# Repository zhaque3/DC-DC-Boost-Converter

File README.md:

# DC Boost Board

**Project:** DC Boost Board — a programmable boost converter for the University of Alberta EcoCar 2025 Prototype Vehicle. The vehicle (Sally) won first place at the Shell Eco Marathon 2025 in the Hydrogen Fuel Cell Prototype Category. 

**Purpose:** This board takes the vehicle's hydrogen fuel cell output voltage (nominally 24 V) and provides a controllable boosted output (typical target: 48 V) for the motor controller and motor. It includes measurement (voltage/current sensing), safety/protection (eFuses and monitoring), an MCU running FreeRTOS for control and telemetry, a simple local UI (OLED + push buttons), and CAN bus communication with other boards on the vehicle and wireless base station.

---

## Table of contents

1. [Key features](#key-features)
2. [Hardware details](#hardware-details)
3. [FreeRTOS firmware overview](#freertos-firmware-overview-what-is-actually-running-on-board)

---

## Key features

* **LM5123** synchronous boost controller driving external mosfets for high-efficiency boost operation.
* Programmable dynamic voltage tuning controlled by MCU and local UI.
* Input/Output: nominal 24 V. The board is designed to output 48V but is capable of outputting 57. 
* **Input / output voltage sensing** and **current sensing** using ADCs and filtering. Firmware computes averaged values before publishing them to the display and logs.
* **TPS2623 eFuses** for controlled power delivery and overcurrent protection.
* **Local UI**: small OLED display (SSD1306) + push buttons for interaction. The display shows input/output voltages, currents, and an effeciency score.
* **FreeRTOS-based firmware** with multiple tasks handling ADC acquisition, DAC control for the tracking/virtual voltage (TRK) pin, LED/status handling, screen updates, and CAN bus communication.

---

## Hardware details

### Synchronous boost controller

* The Texas Instruments LM5123 is used as the switching controller. It drives external mosfets located at the back of the board. The 4 high and low side mosfets can be place on this board. 
* The ENABLE pin from the boost controller is driven by the MCU to allow safe startup/shutdown sequences (the code waits until input voltage is above a small threshold, then toggles ENABLE with a startup delay).
* The TRK (tracking) reference to the controller is driven by the MCU DAC to set the desired output. The firmware converts the `SET_VOLT` value to an appropriate DAC code.

### Sensing

* Voltage sensing is implemented with resistor dividers feeding ADCs.
* Current sensing is performed by hall-effect current sensors that outputs an ADC value to the MCU. 
* ADC sampling is done via DMA for efficiency

### Microcontroller

* The board is built around an STM32G91KUE6 microcontroller, which serves as the central control, sensing, and communication unit for the boost system.
* The MCU runs a FreeRTOS-based firmware architecture, allowing concurrent handling of power control, sensing, UI updates, and CAN communication without blocking critical control paths.

---

## FreeRTOS firmware overview

The firmware running on the DC Boost Board is FreeRTOS based and implemented entirely in `app_freertos.c`.  
The system is structured as a set of independent FreeRTOS tasks, each responsible for a specific functional domain: power control, sensing, user interface, and vehicle communication.

## Tasks (as implemented in `app_freertos.c`)

### DefaultTask (`StartDefaultTask`)

- Initializes the USB CDC device at startup for debug telemetry.
- Implements ENABLE pin sequencing for the LM5123 boost controller:
  - Continuously monitors input voltage.
  - Applies a one-time startup delay before asserting ENABLE once sufficient input voltage is detected.
  - Forces ENABLE low if input voltage falls below threshold and resets the startup sequence.
- Handles a push-button input to increment the output voltage setpoint (`SET_VOLT`) with bounds checking based on input voltage.

### ADC Conversion Task (`StartAdcConv`)

- Starts **ADC peripherals with DMA** for continuous sampling.
- Measures:
  - Input voltage
  - Output voltage
  - Input current
  - Output current
- Applies a 50-sample moving average to current measurements for noise reduction.
- Computes a real-time efficiency estimate using measured voltage and current values.
- Publishes computed values into CAN data structures and prints debug telemetry over USB CDC.

### Screen Print Task (`startScreenPrint`)

- Drives an **SSD1306 OLED display**.
- Displays:
  - Voltage setpoint
  - Input and output voltages
  - Input and output currents
  - Computed efficiency
- When a fault or lock condition is received over CAN, the display switches to an alarm state.

### TRK Pin Control Task (`StartTRKPin`)

- Controls the LM5123 TRK (tracking) pin using the on-chip DAC.
- Converts `SET_VOLT` into a proportional DAC output corresponding to the desired boost output voltage.

### Status LED Task (`StartStatusLED`)

- Controls multiple PWM-driven status LEDs using STM32 timer peripherals.
- LED indications include:
  - Boost ENABLE state
  - General system activity
- Continuously monitors the ENABLE GPIO to synchronize LED states with actual hardware behavior.

## CAN Bus Communication

- Uses the STM32 FDCAN peripheral for vehicle network communication.
- CAN reception is interrupt-driven and handled via the RX FIFO callback, with received frames pushed into FreeRTOS message queues.
- A dedicated receive task parses incoming CAN messages to:
  - Detect fault or lock conditions (e.g. hydrogen alarm states).
  - Update system behavior and UI state.
- A dedicated transmit task periodically publishes:
  - Input and output voltages
  - Input and output currents
  - Efficiency
  - System status flags
- CAN messaging enables real-time monitoring by other PCB's on the vehicle and the wireless telemetry system.

---

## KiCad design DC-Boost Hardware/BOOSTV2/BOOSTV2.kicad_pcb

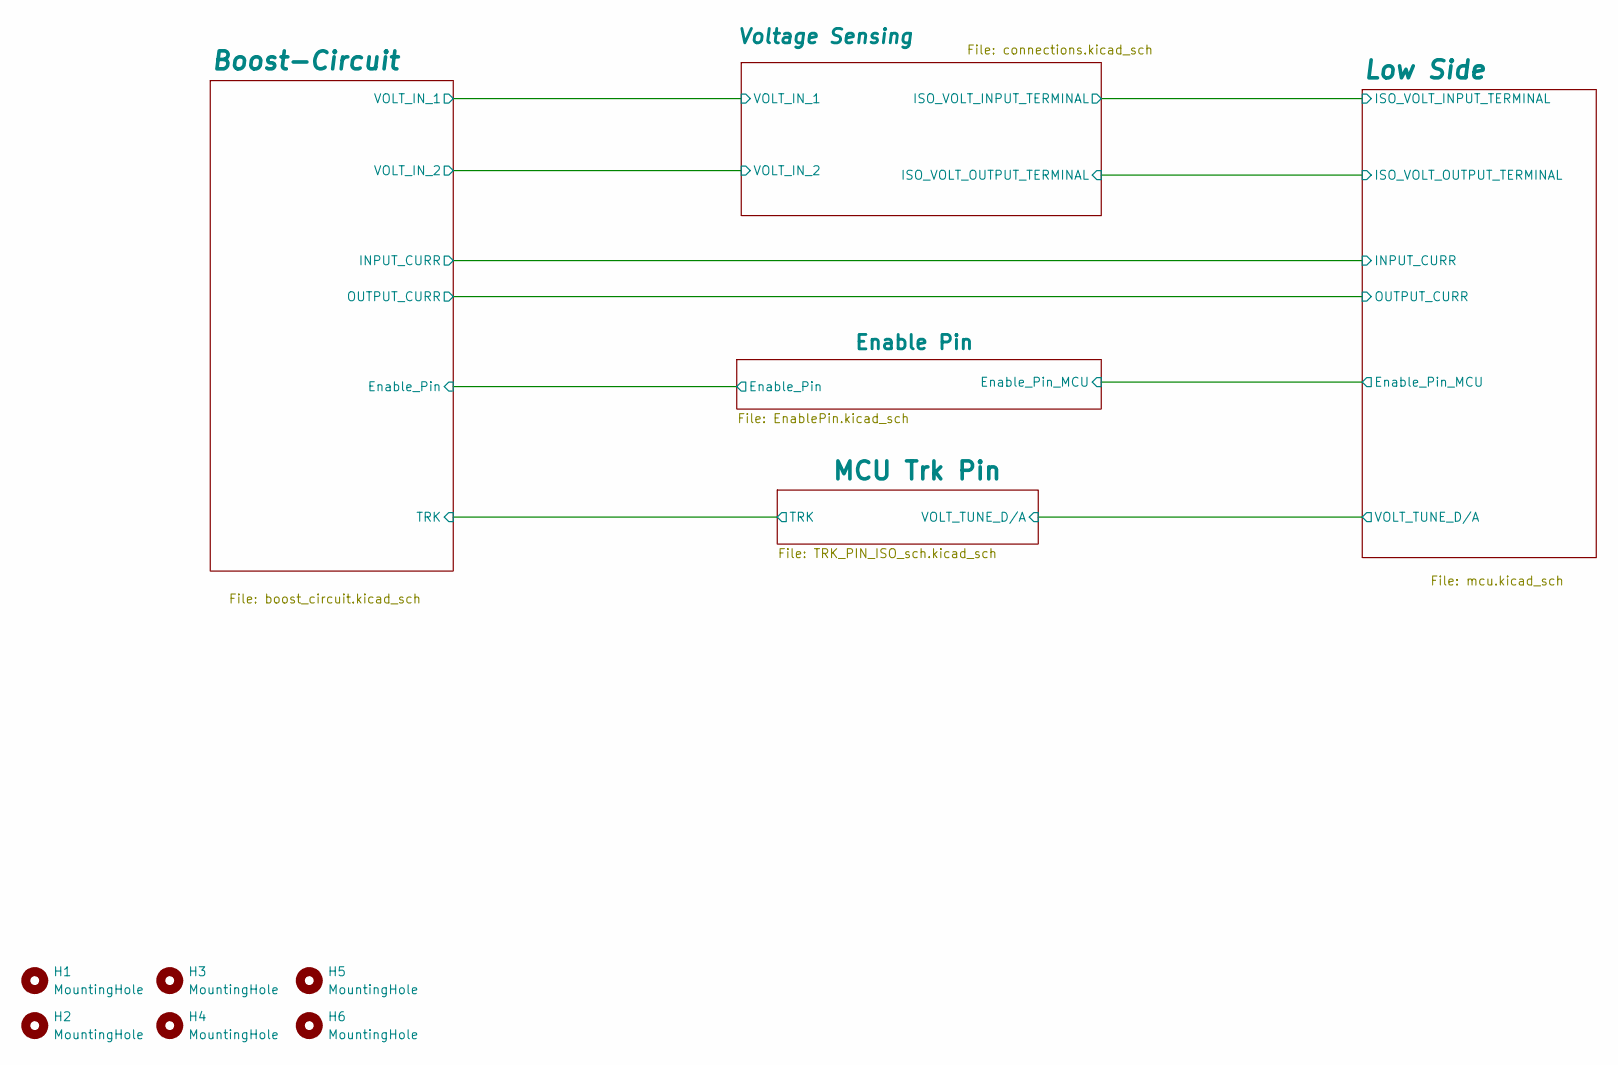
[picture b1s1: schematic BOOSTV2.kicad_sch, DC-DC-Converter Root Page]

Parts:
H1, H2, H3, H4, H5, H6: MountingHole; MountingHole_3.5mm

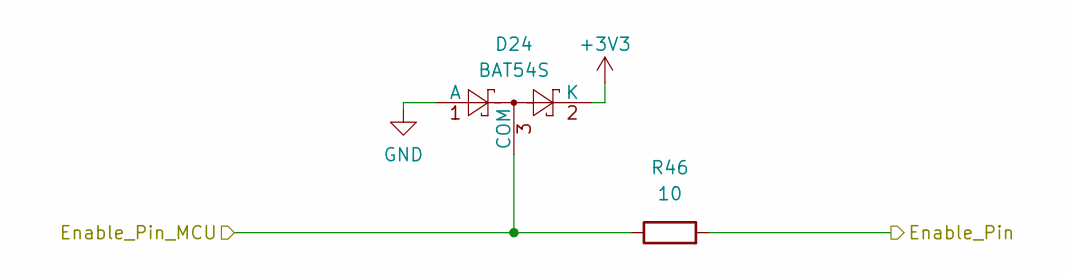
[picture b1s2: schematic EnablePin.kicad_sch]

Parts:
D24: BAT54S; SOT-23
R46: 10; R_0603_1608Metric

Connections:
+3V3: D24.2 (K); also elsewhere on the board
/Boost-Circuit/Enable_Pin: R46.2; also elsewhere on the board
/Enable Pin/Enable_Pin_MCU: D24.3 (COM), R46.1; also elsewhere on the board
GND: D24.1 (A); also elsewhere on the board

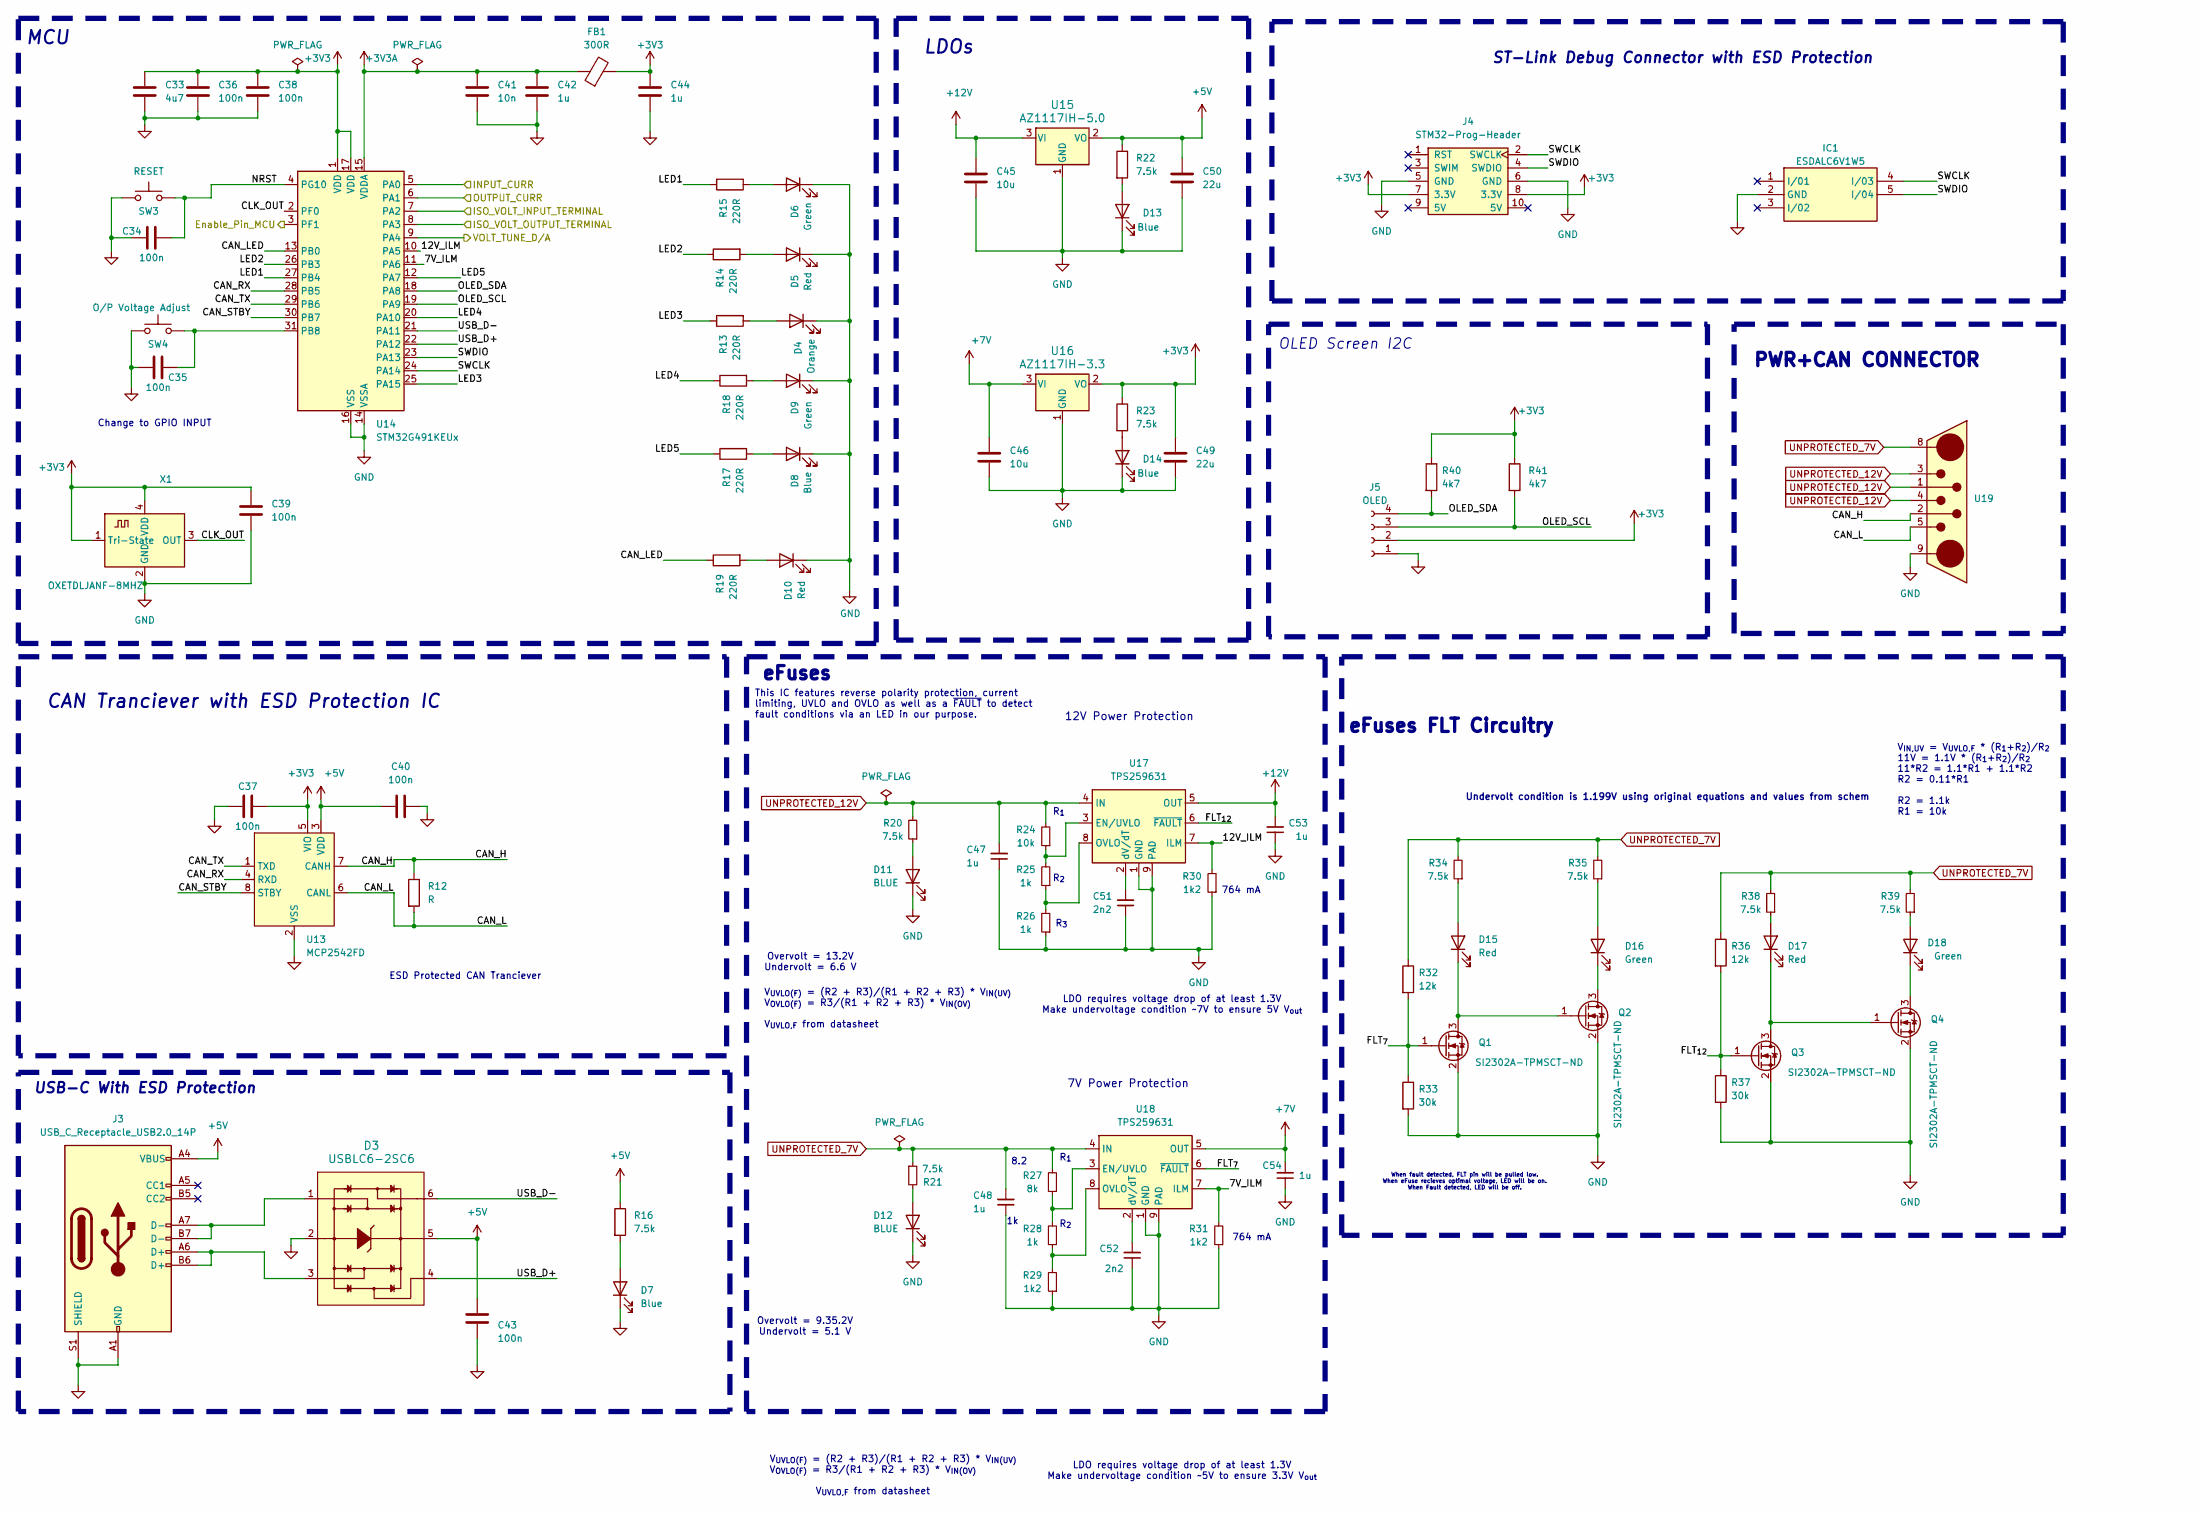
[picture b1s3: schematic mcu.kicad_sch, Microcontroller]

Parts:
C33: 4u7; C_0603_1608Metric; JLCPCB Part#(Optional) C96446
C34, C35, C36, C37, C38, C40, C43: 100n; C_0603_1608Metric; JLCPCB Part#(Optional) C1525
C39: 100n; C_0603_1608Metric
C41: 10n; C_0603_1608Metric; JLCPCB Part#(Optional) C96446
C42, C44: 1u; C_0603_1608Metric; JLCPCB Part#(Optional) C28323
C45, C46: 10u; C_0603_1608Metric
C47, C48, C53, C54: 1u; C_0603_1608Metric; Part# C15849
C49, C50: 22u; C_0603_1608Metric
C51, C52: 2n2; C_0603_1608Metric; Part# C1604
D3: USBLC6-2SC6; SOT95P280X145-6N; Digikey # 497-5235-1-ND
D4: Orange; LED_0603_1608Metric
D5, D10: Red; LED_0603_1608Metric
D6, D9: Green; LED_0603_1608Metric
D7, D8, D13, D14: Blue; LED_0603_1608Metric
D11, D12: BLUE; LED_0603_1608Metric; Part# C72041
D15, D17: Red; LED_0603_1608Metric; Part# C72043
D16, D18: Green; LED_0603_1608Metric; Part# C72043
FB1: 300R; L_0603_1608Metric; Digikey # 1934-1474-1-ND
IC1: ESDALC6V1W5; SOT65P210X110-5N; JLCPCB Part#(Optional) C2827626
J3: USB_C_Receptacle_USB2.0_14P; USB_C_Receptacle_GCT_USB4105-xx-A_16P_TopMnt_Horizontal
J4: STM32-Prog-Header; IDC-STM32-Prog-Header_2x05_P2.54mm_Vertical
J5: OLED; Display_128x64_096_I2C
Q1, Q2, Q3, Q4: SI2302A-TPMSCT-ND; SOT-23-3_Adjusted; Part# SI2302A-TPMSCT-ND
R12: R; R_0603_1608Metric
R13, R14, R15, R17, R18, R19: 220R; R_0603_1608Metric
R16, R22, R23: 7.5k; R_0603_1608Metric
R20: 7.5k; R_0603_1608Metric; Part# C23253
R21, R34, R35, R38, R39: 7.5k; R_0603_1608Metric; Part# C22966
R24: 10k; R_0603_1608Metric
R25, R26, R28: 1k; R_0603_1608Metric
R27: 8k; R_0603_1608Metric
R29, R30, R31: 1k2; R_0603_1608Metric
R32, R36: 12k; R_0603_1608Metric
R33, R37: 30k; R_0603_1608Metric
R40, R41: 4k7; R_0603_1608Metric
SW3: RESET; SW_PUSH_6mm_H5mm; Part # C2689510
SW4: O/P Voltage Adjust; SW_PUSH_6mm_H5mm; Part # C2689510
U13: MCP2542FD; SOIC-8_3.9x4.9mm_P1.27mm
U14: STM32G491KEUx; QFN-32-1EP_5x5mm_P0.5mm_EP3.45x3.45mm
U15: AZ1117IH-5.0; SOT-223-3_TabPin2
U16: AZ1117IH-3.3; SOT-223-3_TabPin2
U17, U18: TPS259631; TI_SO-PowerPAD-8
U19: DB7W2-Male
X1: OXETDLJANF-8MHZ; Crystal_SMD_3225-4Pin_3.2x2.5mm

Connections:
+3V3: C33.1, C36.1, C37.2, C38.1, C39.1, C44.1, C49.1, FB1.2, J4.7 (3.3V), J4.8 (3.3V), J5.2, R23.1, R40.1, R41.1, U13.5 (VIO), U14.1 (VDD), U14.17 (VDD), U16.2 (VO), X1.1 (Tri-State), X1.4 (VDD); also elsewhere on the board
+3V3A: C41.1, C42.1, FB1.1, U14.15 (VDDA)
+5V: C40.2, C43.2, C50.1, D3.5, J3.A4 (VBUS), J3.A9 (VBUS), J3.B4 (VBUS), J3.B9 (VBUS), R16.1, R22.1, U13.3 (VDD), U15.2 (VO); also elsewhere on the board
+7V: C46.1, C54.2, U16.3 (VI), U18.5 (OUT)
+12V: C45.1, C53.2, U15.3 (VI), U17.5 (OUT)
/Boost-Circuit/INPUT_CURR: U14.5 (PA0); also elsewhere on the board
/Boost-Circuit/OUTPUT_CURR: U14.6 (PA1); also elsewhere on the board
/Enable Pin/Enable_Pin_MCU: U14.3 (PF1); also elsewhere on the board
/Low Side/7V_ILM: R31.2, U14.11 (PA6), U18.7 (ILM)
/Low Side/12V_ILM: R30.2, U14.10 (PA5), U17.7 (ILM)
/Low Side/CAN_H: R12.1, U13.7 (CANH), U19.2
/Low Side/CAN_L: R12.2, U13.6 (CANL), U19.5
/Low Side/CAN_LED: R19.1, U14.13 (PB0)
/Low Side/CAN_RX: U13.4 (RXD), U14.28 (PB5)
/Low Side/CAN_STBY: U13.8 (STBY), U14.30 (PB7)
/Low Side/CAN_TX: U13.1 (TXD), U14.29 (PB6)
/Low Side/CLK_OUT: U14.2 (PF0), X1.3 (OUT)
/Low Side/FLT_{7}: Q1.1 (G), R32.2, R33.1, U18.6 (~FAULT)
/Low Side/FLT_{12}: Q3.1 (G), R36.2, R37.1, U17.6 (~FAULT)
/Low Side/ISO_VOLT_INPUT_TERMINAL: U14.7 (PA2); also elsewhere on the board
/Low Side/ISO_VOLT_OUTPUT_TERMINAL: U14.8 (PA3); also elsewhere on the board
/Low Side/LED1: R15.1, U14.27 (PB4)
/Low Side/LED2: R14.1, U14.26 (PB3)
/Low Side/LED3: R13.1, U14.25 (PA15)
/Low Side/LED4: R18.1, U14.20 (PA10)
/Low Side/LED5: R17.1, U14.12 (PA7)
/Low Side/NRST: C34.2, SW3.2, U14.4 (PG10)
/Low Side/OLED_SCL: J5.3, R41.2, U14.19 (PA9)
/Low Side/OLED_SDA: J5.4, R40.2, U14.18 (PA8)
/Low Side/SWCLK: IC1.4 (I/03), J4.2 (SWCLK), U14.24 (PA14)
/Low Side/SWDIO: IC1.5 (I/04), J4.4 (SWDIO), U14.23 (PA13)
/Low Side/USB_D+: D3.4, U14.22 (PA12)
/Low Side/USB_D-: D3.6, U14.21 (PA11)
/Low Side/VOLT_TUNE_D/A: U14.9 (PA4); also elsewhere on the board
GND: C33.2, C34.1, C35.1, C36.2, C37.1, C38.2, C39.2, C40.1, C41.2, C42.2, C43.1, C44.2, C45.2, C46.2, C47.1, C48.1, C49.2, C50.2, C51.1, C52.1, C53.1, C54.1, D3.2, D4.1 (K), D5.1 (K), D6.1 (K), D7.1 (K), D8.1 (K), D9.1 (K), D10.1 (K), D11.1 (K), D12.1 (K), D13.1 (K), D14.1 (K), IC1.2 (GND), J3.A1 (GND), J3.A12 (GND), J3.B1 (GND), J3.B12 (GND), J3.S1 (SHIELD), J4.5 (GND), J4.6 (GND), J5.1, Q1.2 (S), Q2.2 (S), Q3.2 (S), Q4.2 (S), R26.1, R29.1, R30.1, R31.1, R33.2, R37.2, SW3.1, SW4.2, U13.2 (VSS), U14.14 (VSSA), U14.16 (VSS), U14.32 (VSS), U14.33 (VSS), U15.1 (GND), U16.1 (GND), U17.1 (GND), U17.9 (PAD), U18.1 (GND), U18.9 (PAD), U19.9, X1.2 (GND); also elsewhere on the board
unnamed: D3.1, J3.A7 (D-), J3.B7 (D-)
unnamed: D3.3, J3.A6 (D+), J3.B6 (D+)
unnamed: D4.2 (A), R13.2
unnamed: D5.2 (A), R14.2
unnamed: D6.2 (A), R15.2
unnamed: D7.2 (A), R16.2
unnamed: D8.2 (A), R17.2
unnamed: D9.2 (A), R18.2
unnamed: D10.2 (A), R19.2
unnamed: D11.2 (A), R20.1
unnamed: D12.2 (A), R21.2
unnamed: D13.2 (A), R22.2
unnamed: D14.2 (A), R23.2
unnamed: D15.2 (A), R34.1
unnamed: D15.1 (K), Q1.3 (D), Q2.1 (G)
unnamed: D16.2 (A), R35.1
unnamed: D16.1 (K), Q2.3 (D)
unnamed: D17.2 (A), R38.1
unnamed: D17.1 (K), Q3.3 (D), Q4.1 (G)
unnamed: D18.2 (A), R39.1
unnamed: D18.1 (K), Q4.3 (D)
unnamed: C35.2, SW4.1, U14.31 (PB8)
unnamed: R24.1, R25.2, U17.3 (EN/UVLO)
unnamed: R25.1, R26.2, U17.8 (OVLO)
unnamed: C51.2, U17.2 (dV/dT)
unnamed: R27.1, R28.2, U18.3 (EN/UVLO)
unnamed: R28.1, R29.2, U18.8 (OVLO)
unnamed: C52.2, U18.2 (dV/dT)
UNPROTECTED_7V: C48.2, R21.1, R27.2, R32.1, R34.2, R35.2, R36.1, R38.2, R39.2, U18.4 (IN), U19.8
UNPROTECTED_12V: C47.2, R20.2, R24.2, U17.4 (IN), U19.1, U19.3, U19.4

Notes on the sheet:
764 mA
V_{UVLO(F)} = (R2 + R3)/(R1 + R2 + R3) * V_{IN(UV)} V_{OVLO(F)} = R3/(R1 + R2 + R3) * V_{IN(OV)} V_{UVLO,F} from datasheet
V_{IN,UV} = V_{UVLO,F} * (R_{1}+R_{2})/R_{2} 11V = 1.1V * (R_{1}+R_{2})/R_{2} 11*R2 = 1.1*R1 + 1.1*R2 R2 = 0.11*R1 R2 = 1.1k R1 = 10k
MCU
Undervolt condition is 1.199V using original equations and values from schem
LDO requires voltage drop of at least 1.3V Make undervoltage condition ~7V to ensure 5V V_{out}
Overvolt = 13.2V Undervolt = 6.6 V
PWR+CAN CONNECTOR
ST-Link Debug Connector with ESD Protection
8.2
USB-C With ESD Protection
R_{1}
LDOs
CAN Tranciever with ESD Protection IC
R_{2}
LDO requires voltage drop of at least 1.3V Make undervoltage condition ~5V to ensure 3.3V V_{out}
When fault detected, FLT pin will be pulled low. When eFuse recieves optimal voltage, LED will be on. When Fault detected, LED will be off.
Change to GPIO INPUT
eFuses
ESD Protected CAN Tranciever
This IC features reverse polarity protection, current limiting, UVLO and OVLO as well as a ~{FAULT} to detect fault conditions via an LED in our purpose.
V_{UVLO(F)} = (R2 + R3)/(R1 + R2 + R3) * V_{IN(UV)} V_{OVLO(F)} = R3/(R1 + R2 + R3) * V_{IN(OV)} V_{UVLO,F} from datasheet
Overvolt = 9.35.2V Undervolt = 5.1 V
7V Power Protection
OLED Screen I2C
R_{3}
12V Power Protection
eFuses FLT Circuitry

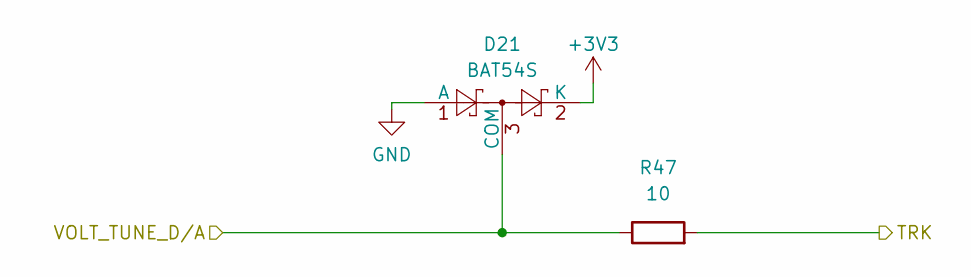
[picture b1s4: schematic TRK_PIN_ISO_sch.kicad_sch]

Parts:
D21: BAT54S; SOT-23
R47: 10; R_0603_1608Metric

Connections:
+3V3: D21.2 (K); also elsewhere on the board
/Boost-Circuit/TRK: R47.2; also elsewhere on the board
/Low Side/VOLT_TUNE_D/A: D21.3 (COM), R47.1; also elsewhere on the board
GND: D21.1 (A); also elsewhere on the board

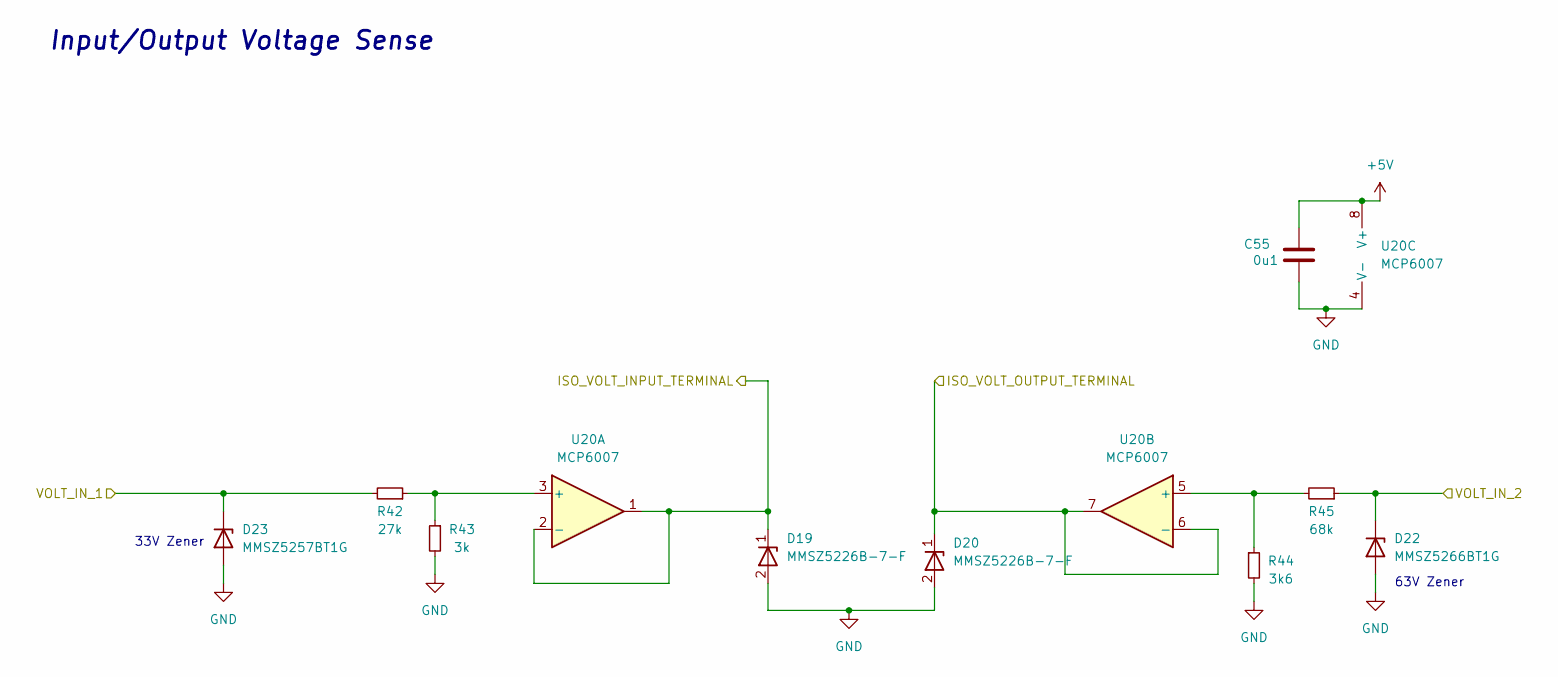
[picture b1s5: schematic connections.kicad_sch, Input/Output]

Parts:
C55: 0u1; C_0603_1608Metric
D19, D20: MMSZ5226B-7-F; D_SOD_123_M; Part# C155250
D22: MMSZ5266BT1G; D_SOD-123
D23: MMSZ5257BT1G; D_SOD-123
R42: 27k; R_0603_1608Metric
R43: 3k; R_0603_1608Metric; Part# C25811
R44: 3k6; R_0603_1608Metric
R45: 68k; R_0603_1608Metric
U20: MCP6007; SOIC-8_3.9x4.9mm_P1.27mm

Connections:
+5V: C55.1, U20.8 (V+); also elsewhere on the board
/Boost-Circuit/VOLT_IN_1: D23.1 (K), R42.2; also elsewhere on the board
/Boost-Circuit/VOLT_IN_2: D22.1 (K), R45.1; also elsewhere on the board
/Low Side/ISO_VOLT_INPUT_TERMINAL: D19.1, U20.1, U20.2 (-); also elsewhere on the board
/Low Side/ISO_VOLT_OUTPUT_TERMINAL: D20.1, U20.6 (-), U20.7; also elsewhere on the board
GND: C55.2, D19.2, D20.2, D22.2 (A), D23.2 (A), R43.2, R44.2, U20.4 (V-); also elsewhere on the board
unnamed: R42.1, R43.1, U20.3 (+)
unnamed: R44.1, R45.2, U20.5 (+)

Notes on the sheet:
33V Zener
Input/Output Voltage Sense
63V Zener

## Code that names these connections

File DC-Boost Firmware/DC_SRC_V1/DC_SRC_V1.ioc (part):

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Mcu.Name=STM32G491K(C-E)Ux
Mcu.Package=UFQFPN32
Mcu.UserName=STM32G491KEUx
PA0.GPIOParameters=GPIO_Label
PA0.GPIO_Label=INPUT_CURR
PA0.Mode=IN1-Single-Ended
PA0.Signal=ADC1_IN1
PA1.GPIOParameters=GPIO_Label
PA1.GPIO_Label=OUTPUT_CURR
PA1.Mode=IN2-Single-Ended
PA1.Signal=ADC1_IN2
PA10.GPIOParameters=GPIO_Label
PA10.GPIO_Label=LED4
PA10.Signal=S_TIM1_CH3
PA11.GPIOParameters=GPIO_Label
PA11.GPIO_Label=USB_D-
PA11.Mode=Device
PA11.Signal=USB_DM
PA12.GPIOParameters=GPIO_Label
PA12.GPIO_Label=USB_D+
PA12.Mode=Device
PA12.Signal=USB_DP
PA13.Mode=Serial_Wire
PA13.Signal=SYS_JTMS-SWDIO
PA14.Mode=Serial_Wire
PA14.Signal=SYS_JTCK-SWCLK
PA15.GPIOParameters=GPIO_Label
PA15.GPIO_Label=LED3
PA15.Signal=S_TIM8_CH1
PA2.GPIOParameters=GPIO_Label
PA2.GPIO_Label=ISO_VOLT_INPUT_TERMINAL
PA2.Mode=IN3-Single-Ended
PA2.Signal=ADC1_IN3
PA3.GPIOParameters=GPIO_Label
PA3.GPIO_Label=ISO_VOLT_OUTPUT_TERMINAL
PA3.Mode=IN4-Single-Ended
PA3.Signal=ADC1_IN4
PA4.Signal=COMP_DAC11_group
PA5.GPIOParameters=GPIO_Label
PA5.GPIO_Label=ADC_12V_ILM
PA5.Mode=IN13-Single-Ended
PA5.Signal=ADC2_IN13
PA6.GPIOParameters=GPIO_Label
PA6.GPIO_Label=ADC_7V_ILM
PA6.Mode=IN3-Single-Ended
PA6.Signal=ADC2_IN3
PA7.GPIOParameters=GPIO_Label
PA7.GPIO_Label=LED5
PA7.Signal=S_TIM3_CH2
PA8.GPIOParameters=GPIO_Label
PA8.GPIO_Label=OLED_SDA
PA8.Mode=I2C
PA8.Signal=I2C2_SDA
PA9.GPIOParameters=GPIO_Label
PA9.GPIO_Label=OLED_SCL
PA9.Mode=I2C
PA9.Signal=I2C2_SCL
PB0.GPIOParameters=GPIO_Label
PB0.GPIO_Label=CAN_LED
PB0.Signal=S_TIM3_CH3
PB3.GPIOParameters=GPIO_Label
PB3.GPIO_Label=LED2
PB3.Signal=S_TIM2_CH2
PB4.GPIOParameters=GPIO_Label
PB4.GPIO_Label=LED1
PB4.Signal=S_TIM3_CH1
PB5.GPIOParameters=GPIO_PuPd
PB5.GPIO_PuPd=GPIO_PULLUP
PB5.Mode=FDCAN_Activate
PB5.Signal=FDCAN2_RX
PB6.Mode=FDCAN_Activate
PB6.Signal=FDCAN2_TX
PB7.GPIOParameters=GPIO_Label
PB7.GPIO_Label=CAN_STBY
PB7.Signal=GPIO_Output
PB8-BOOT0.GPIOParameters=GPIO_PuPd,GPIO_Label
PB8-BOOT0.GPIO_Label=Toggle
PB8-BOOT0.GPIO_PuPd=GPIO_PULLUP
PB8-BOOT0.Signal=GPIO_Input
PF0-OSC_IN.Mode=HSE-External-Clock-Source
PF0-OSC_IN.Signal=RCC_OSC_IN
PF1-OSC_OUT.GPIOParameters=GPIO_Label
PF1-OSC_OUT.GPIO_Label=ENABLE
PF1-OSC_OUT.Signal=GPIO_Output
RCC.HSE_VALUE=8000000
RCC.SYSCLKFreq_VALUE=170000000
RCC.SYSCLKSource=RCC_SYSCLKSOURCE_PLLCLK
board=custom
